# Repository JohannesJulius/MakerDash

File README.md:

# MakerDash

> Früher „Pico Dashboard“.

Ein selbstgebautes Mischpult für den PC: drei Fader, ein Drehgeber und ein OLED-Display an einem
Raspberry Pi Pico 2 steuern Systemlautstärke, Mikrofon und einzelne Programme unter Windows.

## Funktionen

- **Fader 1/2:** standardmäßig Systemlautstärke und Mikrofon (in der App frei belegbar)
- **Fader 3:** ein Programm oder eine Gruppe nach Wahl – am Dashboard im Menü oder in der App auswählbar
- **Gruppen** wie in Wave Link: mehrere Programme (z. B. alle Spiele) auf einem Fader
- **Alle Fader frei belegbar:** System, Mikrofon, Programm, Gruppe oder das aktive Fenster
- **Stummschalten** per langem Druck auf den Drehgeber, mit Anzeige auf dem Display
- **Panel mit RP2040-Zero:** Bedienelemente und Display an einem eigenen kleinen Board, der Pico als Brücke (siehe `hardware/zero-panel/`)
- **Menü am Dashboard:** Programm für Fader 3, Ausgabegerät und Mikrofon umschalten
- **Display:** Start-Animation, Lautstärke-Anzeige, Bildschirmschoner
- **App:** moderne Oberfläche, Live-Anzeige, Umbenennen/Ausblenden von Programmen und Geräten
- **Firmware-Verwaltung:** Die App spielt die Pico-Software selbst auf und aktualisiert sie
- **Automatische Updates** über GitHub Releases

## Installation

1. Neueste `MakerDash-Setup.exe` unter **Releases** herunterladen und starten.
2. Der Einrichtungsassistent führt durch das Anschließen. Ein neuer Pico wird im BOOTSEL-Modus
   (Taste gedrückt halten und einstecken) erkannt und komplett eingerichtet.

Benötigt Windows 10/11 (64 Bit) mit WebView2 Runtime (bei Windows 11 vorinstalliert).

## Verdrahtung (Standard)

| Bauteil | Pin |
|---|---|
| Fader 1 | GP28 |
| Fader 2 | GP27 |
| Fader 3 | GP26 |
| Encoder A / B / Taster | GP10 / GP11 / GP12 |
| OLED SDA / SCL | GP4 / GP5 |
| Fader & OLED Versorgung | 3V3(OUT), GND |

Die Belegung lässt sich in der App unter **Dashboard → Verdrahtung** ändern.

## Neue Version veröffentlichen

1. Versionsnummer in der Datei `VERSION` erhöhen (z. B. `2.1.0`)
2. optional: Beschreibung in `release-notes/v2.1.0.md` anlegen
3. committen und auf `main` pushen

GitHub baut daraufhin App und Installer (`.github/workflows/release.yml`), legt den Tag `v2.1.0` an
und veröffentlicht alles als Release. (Ein gepushter Tag `v*` funktioniert ebenfalls.)
Installierte Apps finden das Update automatisch. Wird `firmware/code.py` (`FW_VERSION`) geändert,
aktualisiert die App danach auch das Dashboard.

> Das Repository muss **öffentlich** sein, damit die App Updates ohne Anmeldung abrufen kann.

## Aufbau

| Pfad | Inhalt |
|---|---|
| `*.go` | Windows-App (Go, ohne cgo) |
| `ui/index.html` | Oberfläche (läuft in WebView2) |
| `firmware/` | Pico-Firmware (CircuitPython), wird in die App eingebettet |
| `installer/` | NSIS-Installer |
| `hardware/zero-panel/` | Panel mit RP2040-Zero: Fader, Drehgeber und Display, Pico als Brücke |

Lokal bauen (Linux oder Windows, Go ≥ 1.24):

```bash
GOOS=windows GOARCH=amd64 go build -ldflags "-H windowsgui -X main.AppVersion=2.1.0" -o dist/MakerDash.exe .
cd installer && makensis -DVERSION=2.1.0 setup.nsi
```

Die Bibliotheken in `firmware/lib` stammen von Adafruit (MIT-Lizenz).

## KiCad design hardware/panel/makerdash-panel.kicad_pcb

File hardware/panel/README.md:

# MakerDash Panel-Platine v1.0

Zwischenplatine zwischen Pico und Bedienelementen: Fader, Drehgeber, Taster und das Display hängen
an dieser Platine, der Pico ist nur noch über **4 Adern** angeschlossen und belegt **2 GPIOs** (I2C)
statt bisher 8.

## Überblick

| | |
|---|---|
| Größe | 80 × 70 mm, 2 Lagen, 4 Bohrungen M3 (3,5 mm vom Rand) |
| Controller | **AVR64DD28-I/SP** (DIP-28, im Sockel), 3,3 V, interner Takt |
| Versorgung | 5 V vom Pico (VBUS) → eigener Regler **MCP1700-3302E** (3,3 V, 250 mA) |
| Anschluss Pico | JST-XH 4-polig: GND · 5 V · SDA · SCL |
| Kanäle | **16 Universal-Kanäle** K1–K16, je 3 Pins: Signal · +3,3 V · GND |
| Display | Buchse für SSD1306-OLED (I2C), hängt am selben Bus |
| Bauteile | ausschließlich Durchsteck-Bauteile (THT) |

Alle Bauteile werden von Hand gelötet, es gibt keine SMD-Teile.

## Anschluss an den Pico

| Panel J1 „BUS IN“ | Pico 2 |
|---|---|
| 1 GND | GND (z. B. Pin 38) |
| 2 5V | VBUS (Pin 40) |
| 3 SDA | GP4 (Pin 6) – wie bisher das Display |
| 4 SCL | GP5 (Pin 7) |

Der Pico spricht als I2C-Controller mit zwei Teilnehmern: dem Panel-Controller (Adresse **0x30**)
und dem Display (**0x3C**). Über **J2 „BUS OUT“** lassen sich weitere Panels anhängen. Jede Platine
bekommt dann über **JP1/JP2** eine eigene Adresse (0x30–0x33).

**Pull-ups (JP3):** Den Jumper nur auf **einer** Platine am Bus stecken.

## Universal-Kanäle

Jede Kanalleiste: **1 = Signal**, **2 = +3,3 V**, **3 = GND** (Bestückungsdruck „S + –“).

| Bauteil | Anschluss |
|---|---|
| Fader / Poti | Schleifer → 1, Enden → 2 und 3 (ein Ende an +3,3 V, eins an GND) |
| Taster | 1 und 3 (interner Pull-up im Controller) |
| Drehgeber | A an Signal von Kanal n, B an Signal von Kanal n+1, gemeinsamer Pin an GND; Taster als eigener Kanal |
| LED | Signal → Vorwiderstand → LED → GND |

Was ein Kanal ist (analog, Taster, Drehgeber, LED), legt die Firmware bzw. die App fest. Die Platine
ist für alle Panels gleich.

| Kanal | Pin am Chip | analog | | Kanal | Pin am Chip | analog |
|---|---|---|---|---|---|---|
| K1 | PD7 (13) | AIN7 | | K9 | PC2 (4) | AIN30 |
| K2 | PD6 (12) | AIN6 | | K10 | PC1 (3) | AIN29 |
| K3 | PD5 (11) | AIN5 | | K11 | PC0 (2) | AIN28 |
| K4 | PD4 (10) | AIN4 | | K12 | PA7 (1) | AIN27 |
| K5 | PD3 (9) | AIN3 | | K13 | PA4 (26) | AIN24 |
| K6 | PD2 (8) | AIN2 | | K14 | PA5 (27) | AIN25 |
| K7 | PD1 (7) | AIN1 | | K15 | PA6 (28) | AIN26 |
| K8 | PC3 (5) | AIN31 | | K16 | PA1 (23) | nur digital |

Weitere Pins: PA2/PA3 = I2C (SDA/SCL), PA0 = Status-LED, PF0/PF1 = Adress-Jumper, UPDI (19) = Programmieren.

**Für das jetzige Dashboard:** Fader 1–3 an K1–K3, Drehgeber A/B an K4/K5, Drehgeber-Taster an K6,
Display in J3.

## Stückliste

| Ref | Bauteil | Anzahl |
|---|---|---|
| U1 | AVR64DD28-I/SP (DIP-28) | 1 |
| – | IC-Sockel DIP-28, schmal (7,62 mm) | 1 |
| U2 | MCP1700-3302E/TO (TO-92) | 1 |
| C1, C2 | Keramik-Kondensator 1 µF, Rastermaß 5 mm | 2 |
| C3 | Elko 10 µF ≥ 6,3 V, Ø 5 mm, Rastermaß 2 mm | 1 |
| C4, C5, C6 | Keramik-Kondensator 100 nF, Rastermaß 5 mm | 3 |
| R1, R2 | Widerstand 4,7 kΩ (0207) | 2 |
| R3 | Widerstand 1 kΩ (0207) | 1 |
| D1 | LED 3 mm grün | 1 |
| J1, J2 | JST-XH 4-polig stehend (B4B-XH-A) + Stecker XHP-4 und Crimpkontakte | 2 |
| J3 | Buchsenleiste 1×4, 2,54 mm (für das OLED-Modul) | 1 |
| J4 | Stiftleiste 1×3 (UPDI) | 1 |
| J5, JP1, JP2, JP3 | Stiftleiste 1×2 + 3 Jumper | 4 |
| J10–J25 | Stiftleiste 1×3 (Kanäle K1–K16), nur die benötigten bestücken | bis 16 |
| – | Abstandshalter M3 | 4 |

## Platine bestellen

Bestellliste mit Teilenummern: [BESTELLLISTE.md](BESTELLLISTE.md).

`makerdash-panel-gerber.zip` bei einem Platinenhersteller hochladen, z. B. JLCPCB, PCBWay oder
Aisler. Einstellungen: 2 Lagen, 1,6 mm, keine Bestückung. Die Datei enthält Kupfer, Lötstopp,
Bestückungsdruck, Kontur und Bohrdaten.

## Aufbau

1. Flache Teile zuerst: Widerstände, Keramik-Kondensatoren, IC-Sockel (Kerbe nach rechts zu den Bus-Buchsen, Pin 1 oben rechts).
2. Regler U2 (flache Seite wie im Bestückungsdruck), Elko C3 (+ beachten), LED D1 (kurzes Bein = Kathode).
3. Stiftleisten, Buchsenleiste, JST-Buchsen.
4. **Vor dem Einsetzen des Chips:** 5 V anlegen und an J4 Pin 3 bzw. Kanal-Pin 2 **3,3 V** messen.
5. Chip einsetzen.

## Programmieren

Der Controller wird einmalig über **UPDI** (J4: 1 UPDI · 2 GND · 3 +3,3 V) programmiert. Dazu reicht
ein USB-Seriell-Adapter mit 3,3 V nach der SerialUPDI-Anleitung von DxCore. Die Firmware für den
Controller und die Anpassung der Pico-Firmware und der App folgen als nächster Schritt. Bis dahin
funktioniert die Platine noch nicht mit MakerDash.

## Offene Punkte vor der Bestellung

- Die Pinbelegung des AVR64DD28 stammt aus der DxCore-Dokumentation. Im KiCad-Symbol wird der
  pin-kompatible AVR DB28 verwendet. **Vor dem Bestellen gegen das Microchip-Datenblatt
  (DS40002315) prüfen.**
- OLED-Module gibt es mit vertauschten Pins GND/VCC. J3 ist für die Reihenfolge
  **GND · VCC · SCL · SDA** ausgelegt.

## Dateien

| Datei | Inhalt |
|---|---|
| `makerdash-panel.kicad_sch / .kicad_pcb / .kicad_pro` | KiCad-7-Projekt (mit KiCad öffnen und bearbeiten) |
| `makerdash-panel-schaltplan.pdf` | Schaltplan zum Ausdrucken |
| `makerdash-panel-gerber.zip` | Fertigungsdaten |
| `gen_schematic.py`, `gen_pcb.py`, `build.sh` | erzeugen alles neu (Platzierung, Routing mit Freerouting, DRC, Gerber) |

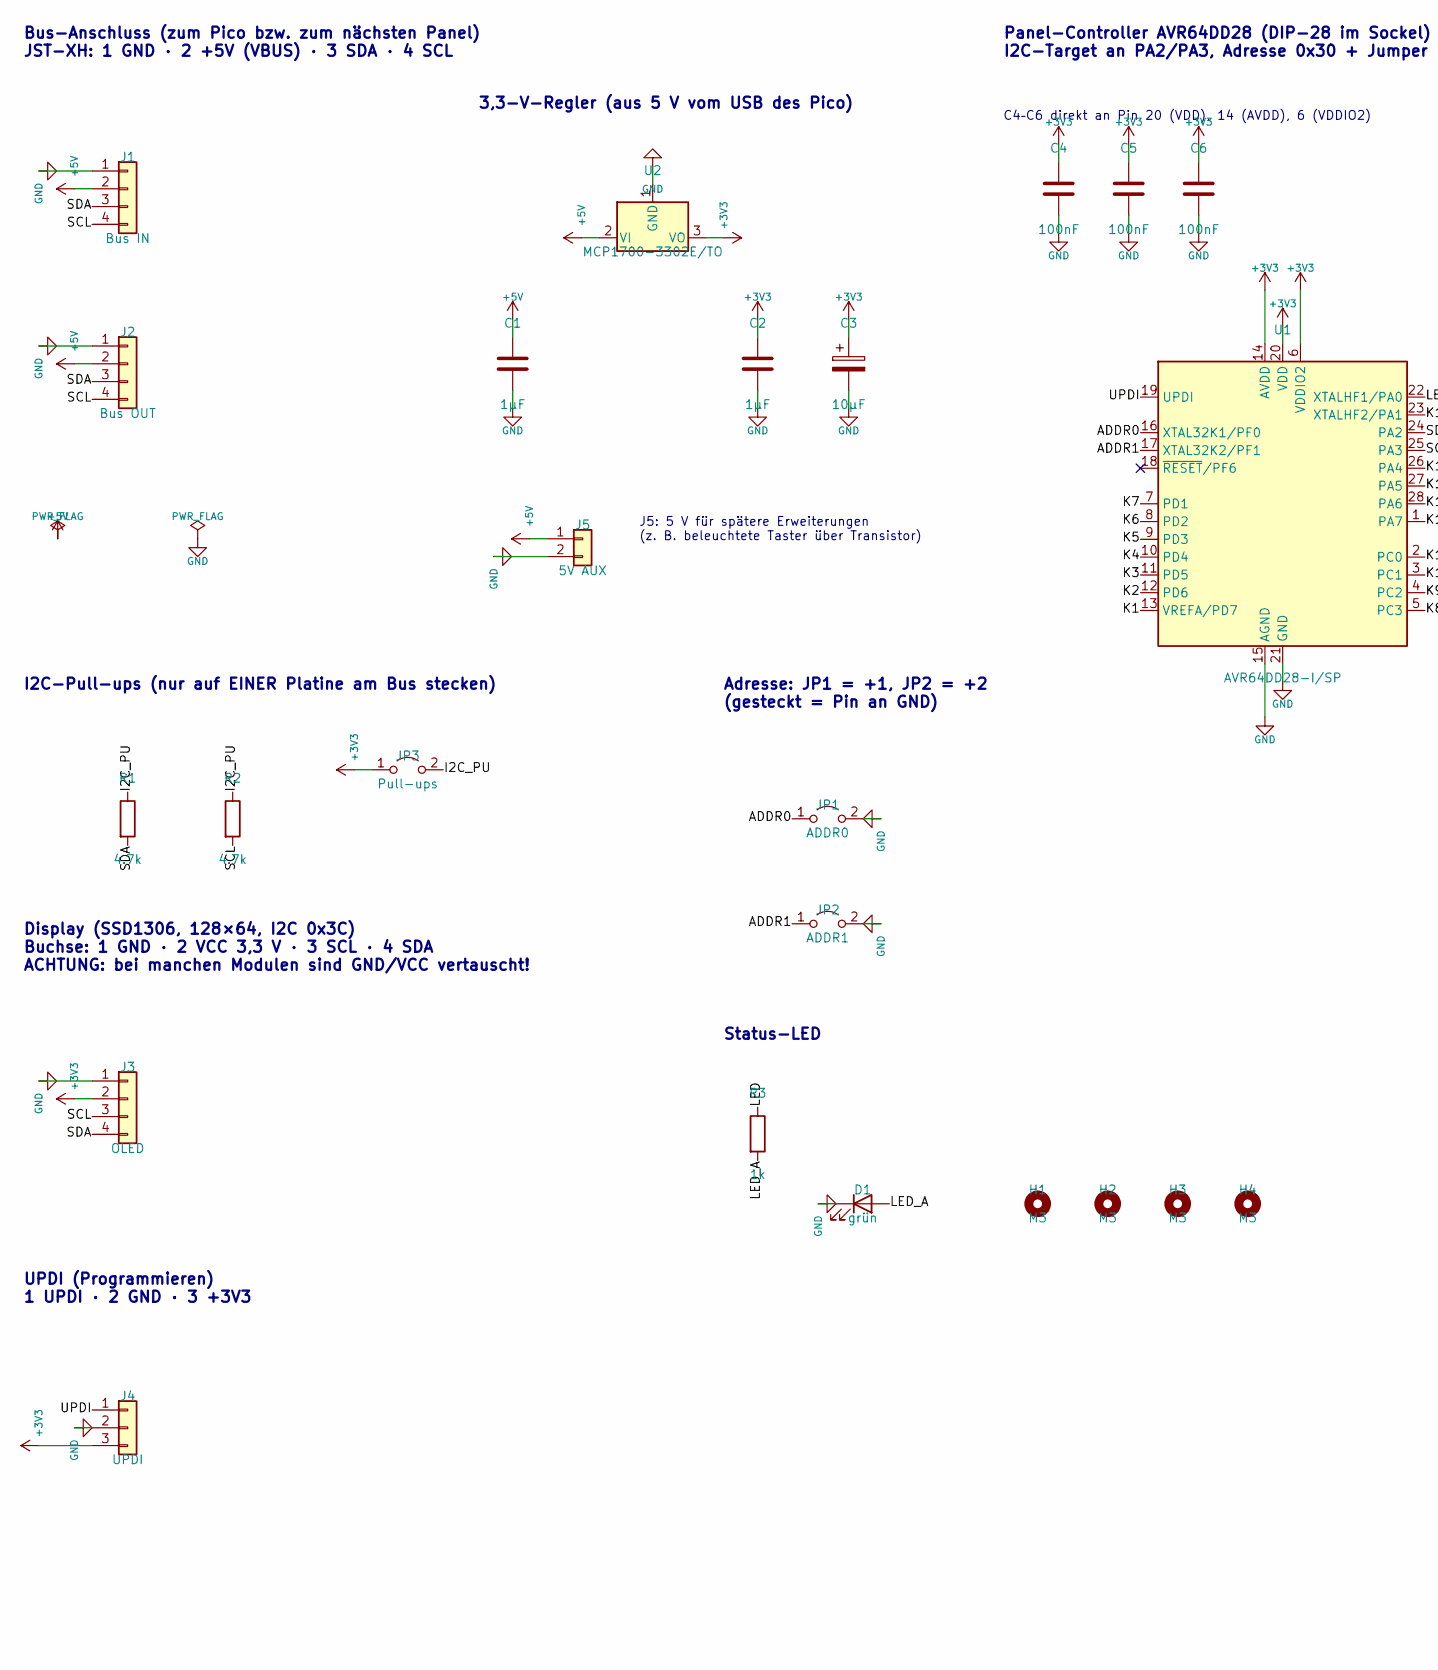
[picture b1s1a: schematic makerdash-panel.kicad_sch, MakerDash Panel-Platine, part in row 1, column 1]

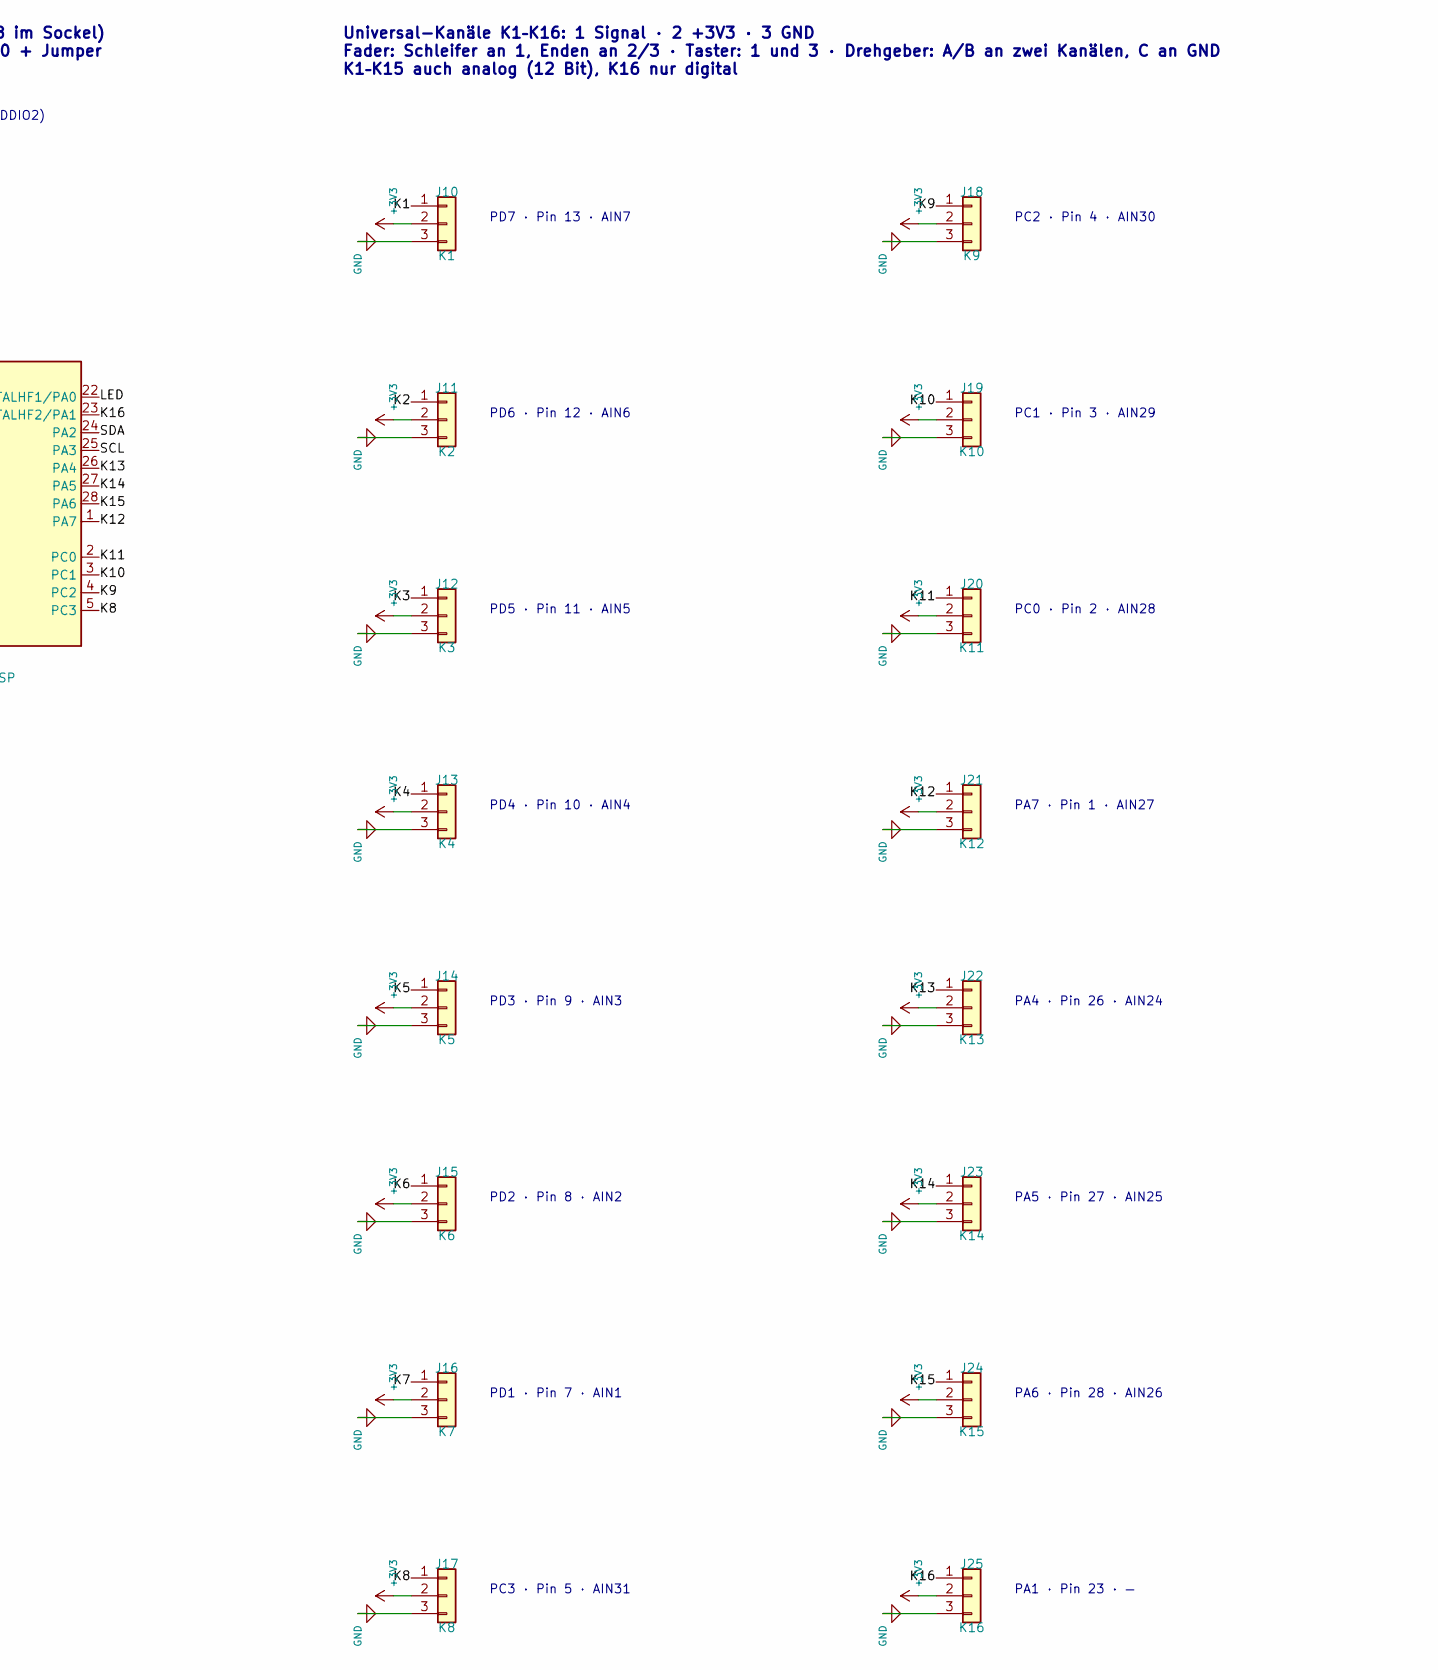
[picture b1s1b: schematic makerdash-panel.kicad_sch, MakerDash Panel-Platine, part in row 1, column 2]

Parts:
C1, C2: 1µF; C_Disc_D5.0mm_W2.5mm_P5.00mm
C3: 10µF; CP_Radial_D5.0mm_P2.00mm
C4, C5, C6: 100nF; C_Disc_D5.0mm_W2.5mm_P5.00mm
D1: grün; LED_D3.0mm
H1, H2, H3, H4: M3; MountingHole_3.2mm_M3
J1: Bus IN; JST_XH_B4B-XH-A_1x04_P2.50mm_Vertical
J2: Bus OUT; JST_XH_B4B-XH-A_1x04_P2.50mm_Vertical
J3: OLED; PinSocket_1x04_P2.54mm_Vertical
J4: UPDI; PinHeader_1x03_P2.54mm_Vertical
J5: 5V AUX; PinHeader_1x02_P2.54mm_Vertical
J10: K1; PinHeader_1x03_P2.54mm_Vertical
J11: K2; PinHeader_1x03_P2.54mm_Vertical
J12: K3; PinHeader_1x03_P2.54mm_Vertical
J13: K4; PinHeader_1x03_P2.54mm_Vertical
J14: K5; PinHeader_1x03_P2.54mm_Vertical
J15: K6; PinHeader_1x03_P2.54mm_Vertical
J16: K7; PinHeader_1x03_P2.54mm_Vertical
J17: K8; PinHeader_1x03_P2.54mm_Vertical
J18: K9; PinHeader_1x03_P2.54mm_Vertical
J19: K10; PinHeader_1x03_P2.54mm_Vertical
J20: K11; PinHeader_1x03_P2.54mm_Vertical
J21: K12; PinHeader_1x03_P2.54mm_Vertical
J22: K13; PinHeader_1x03_P2.54mm_Vertical
J23: K14; PinHeader_1x03_P2.54mm_Vertical
J24: K15; PinHeader_1x03_P2.54mm_Vertical
J25: K16; PinHeader_1x03_P2.54mm_Vertical
JP1: ADDR0; PinHeader_1x02_P2.54mm_Vertical
JP2: ADDR1; PinHeader_1x02_P2.54mm_Vertical
JP3: Pull-ups; PinHeader_1x02_P2.54mm_Vertical
R1, R2: 4.7k; R_Axial_DIN0207_L6.3mm_D2.5mm_P7.62mm_Horizontal
R3: 1k; R_Axial_DIN0207_L6.3mm_D2.5mm_P7.62mm_Horizontal
U1: AVR64DD28-I/SP; DIP-28_W7.62mm_Socket
U2: MCP1700-3302E/TO; TO-92_Inline_Wide

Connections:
+3V3: C2.1, C3.1, C4.1, C5.1, C6.1, J3.2, J4.3, J10.2, J11.2, J12.2, J13.2, J14.2, J15.2, J16.2, J17.2, J18.2, J19.2, J20.2, J21.2, J22.2, J23.2, J24.2, J25.2, JP3.1 (A), U1.6 (VDDIO2), U1.14 (AVDD), U1.20 (VDD), U2.3 (VO)
+5V: C1.1, J1.2, J2.2, J5.1, U2.2 (VI)
ADDR0: JP1.1 (A), U1.16 (XTAL32K1/PF0)
ADDR1: JP2.1 (A), U1.17 (XTAL32K2/PF1)
GND: C1.2, C2.2, C3.2, C4.2, C5.2, C6.2, D1.1 (K), J1.1, J2.1, J3.1, J4.2, J5.2, J10.3, J11.3, J12.3, J13.3, J14.3, J15.3, J16.3, J17.3, J18.3, J19.3, J20.3, J21.3, J22.3, J23.3, J24.3, J25.3, JP1.2 (B), JP2.2 (B), U1.15 (AGND), U1.21 (GND), U2.1 (GND)
I2C_PU: JP3.2 (B), R1.1, R2.1
K1: J10.1, U1.13 (VREFA/PD7)
K2: J11.1, U1.12 (PD6)
K3: J12.1, U1.11 (PD5)
K4: J13.1, U1.10 (PD4)
K5: J14.1, U1.9 (PD3)
K6: J15.1, U1.8 (PD2)
K7: J16.1, U1.7 (PD1)
K8: J17.1, U1.5 (PC3)
K9: J18.1, U1.4 (PC2)
K10: J19.1, U1.3 (PC1)
K11: J20.1, U1.2 (PC0)
K12: J21.1, U1.1 (PA7)
K13: J22.1, U1.26 (PA4)
K14: J23.1, U1.27 (PA5)
K15: J24.1, U1.28 (PA6)
K16: J25.1, U1.23 (XTALHF2/PA1)
LED: R3.1, U1.22 (XTALHF1/PA0)
LED_A: D1.2 (A), R3.2
SCL: J1.4, J2.4, J3.3, R2.2, U1.25 (PA3)
SDA: J1.3, J2.3, J3.4, R1.2, U1.24 (PA2)
UPDI: J4.1, U1.19 (UPDI)

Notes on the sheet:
Bus-Anschluss (zum Pico bzw. zum nächsten Panel) JST-XH: 1 GND · 2 +5V (VBUS) · 3 SDA · 4 SCL
3,3-V-Regler (aus 5 V vom USB des Pico)
J5: 5 V für spätere Erweiterungen (z. B. beleuchtete Taster über Transistor)
Panel-Controller AVR64DD28 (DIP-28 im Sockel) I2C-Target an PA2/PA3, Adresse 0x30 + Jumper
C4–C6 direkt an Pin 20 (VDD), 14 (AVDD), 6 (VDDIO2)
I2C-Pull-ups (nur auf EINER Platine am Bus stecken)
Display (SSD1306, 128×64, I2C 0x3C) Buchse: 1 GND · 2 VCC 3,3 V · 3 SCL · 4 SDA ACHTUNG: bei manchen Modulen sind GND/VCC vertauscht!
UPDI (Programmieren) 1 UPDI · 2 GND · 3 +3V3
Adresse: JP1 = +1, JP2 = +2 (gesteckt = Pin an GND)
Status-LED
Universal-Kanäle K1–K16: 1 Signal · 2 +3V3 · 3 GND Fader: Schleifer an 1, Enden an 2/3 · Taster: 1 und 3 · Drehgeber: A/B an zwei Kanälen, C an GND K1–K15 auch analog (12 Bit), K16 nur digital
PD7 · Pin 13 · AIN7
PD6 · Pin 12 · AIN6
PD5 · Pin 11 · AIN5
PD4 · Pin 10 · AIN4
PD3 · Pin 9 · AIN3
PD2 · Pin 8 · AIN2
PD1 · Pin 7 · AIN1
PC3 · Pin 5 · AIN31
PC2 · Pin 4 · AIN30
PC1 · Pin 3 · AIN29
PC0 · Pin 2 · AIN28
PA7 · Pin 1 · AIN27
PA4 · Pin 26 · AIN24
PA5 · Pin 27 · AIN25
PA6 · Pin 28 · AIN26
PA1 · Pin 23 · —

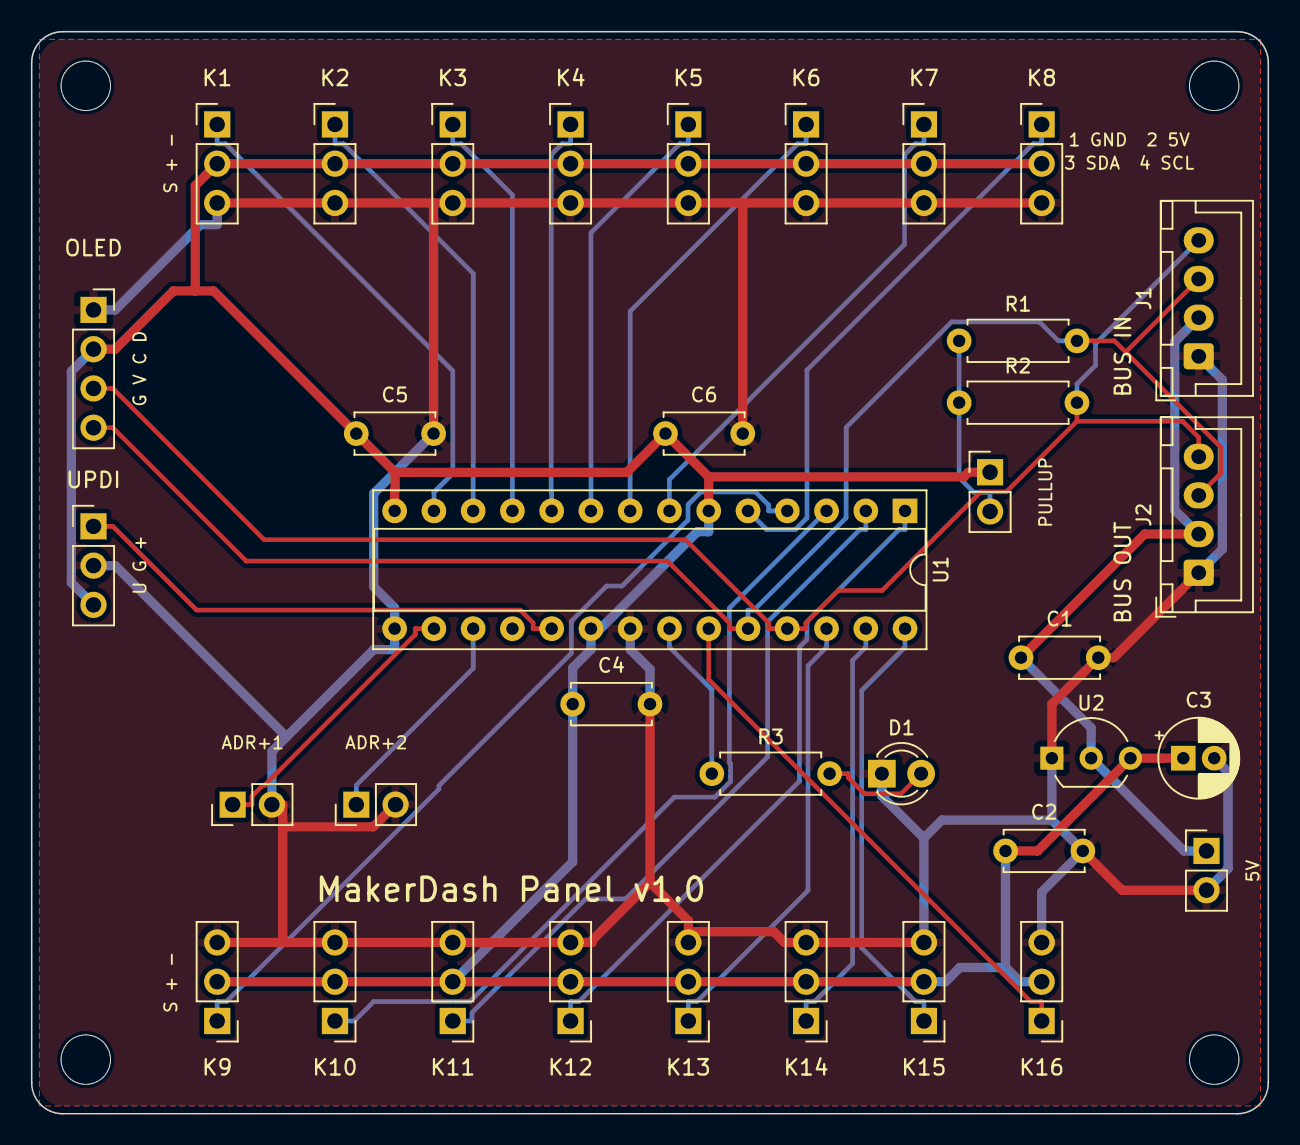
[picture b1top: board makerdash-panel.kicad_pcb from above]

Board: 2 copper layers, 80.0 x 70.0 mm, 40 parts (0 on the bottom side), 27 nets.

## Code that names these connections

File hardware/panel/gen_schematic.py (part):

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
# Universal-Kanäle K1..K16: (Port-Pin, DIP-Pin, Analogeingang)
KANAELE = [  # Reihenfolge nach Lage der Pins auf der Platine (kurze Leiterbahnen)
    ("PD7", 13, "AIN7"), ("PD6", 12, "AIN6"), ("PD5", 11, "AIN5"), ("PD4", 10, "AIN4"),
    ("PD3", 9, "AIN3"), ("PD2", 8, "AIN2"), ("PD1", 7, "AIN1"), ("PC3", 5, "AIN31"),
    ("PC2", 4, "AIN30"), ("PC1", 3, "AIN29"), ("PC0", 2, "AIN28"), ("PA7", 1, "AIN27"),
    ("PA4", 26, "AIN24"), ("PA5", 27, "AIN25"), ("PA6", 28, "AIN26"), ("PA1", 23, "—"),
]


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    C4 = s.sym("C4", "Connector_Generic", "Conn_01x04")
    LDO = s.sym("LDO", "Regulator_Linear", "MCP1700x-330xxTO")
    HOLE = s.sym("HOLE", "Mechanical", "MountingHole")
    # AVR64DD28 ist pinkompatibel zum AVR DB28 aus der KiCad-Bibliothek (Versorgung, UPDI, Ports)
    MCU = s.sym("MCU", "MCU_Microchip_AVR_Dx", "AVR32DB28x-xSO", alias="AVR64DD28-I_SP",
                props={"Value": "AVR64DD28-I/SP", "Footprint": FP["DIP28"]})

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    s.text("J5: 5 V für spätere Erweiterungen\n(z. B. beleuchtete Taster über Transistor)", 108, 92, 1.27)

    # --- Mikrocontroller -------------------------------------------------------------
    s.text("Panel-Controller AVR64DD28 (DIP-28 im Sockel)\nI2C-Target an PA2/PA3, Adresse 0x30 + Jumper", 160, 22, 1.6, True)
    nets = {"14": "PWR:+3V3", "20": "PWR:+3V3", "6": "PWR:+3V3", "15": "PWR:GND", "21": "PWR:GND",
            "24": "SDA", "25": "SCL", "19": "UPDI", "18": "NC", "22": "LED", "16": "ADDR0", "17": "ADDR1"}
    for i, (port, pin, _) in enumerate(KANAELE):
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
